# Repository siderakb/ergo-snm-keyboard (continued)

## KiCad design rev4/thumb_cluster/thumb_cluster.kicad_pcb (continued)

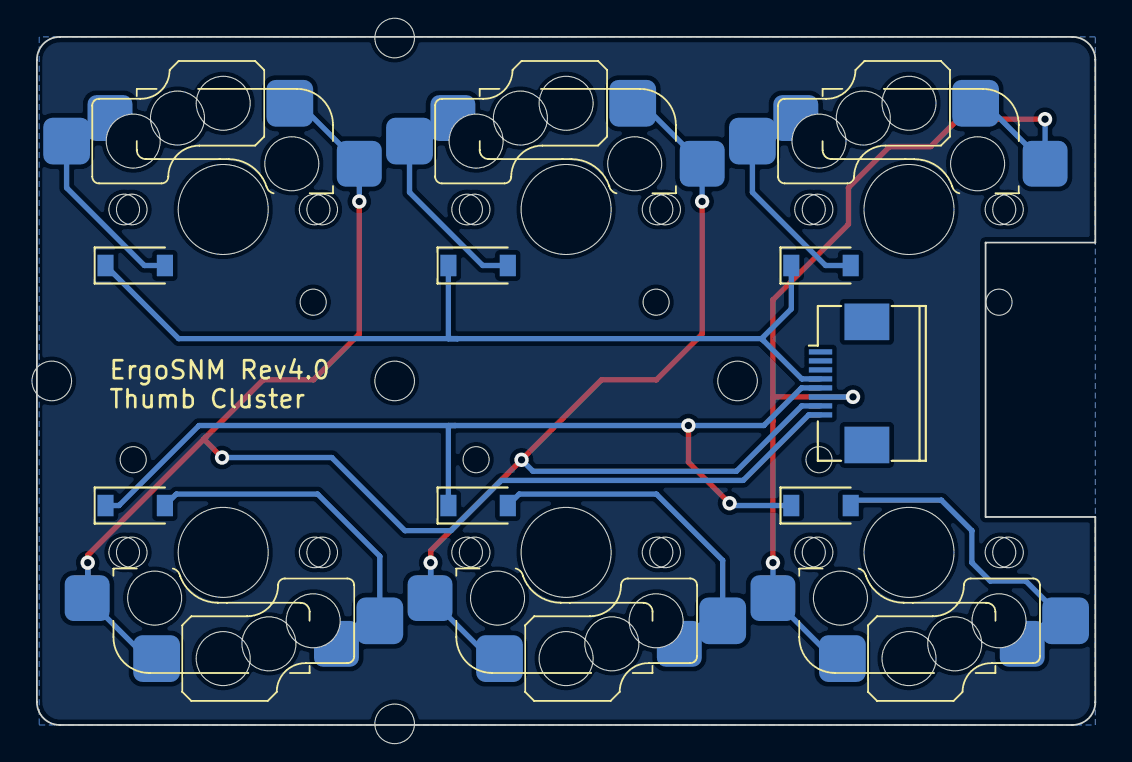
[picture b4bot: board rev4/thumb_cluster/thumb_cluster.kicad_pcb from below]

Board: 2 copper layers, 58.8 x 38.2 mm, 18 parts (11 on the bottom side), 11 nets.

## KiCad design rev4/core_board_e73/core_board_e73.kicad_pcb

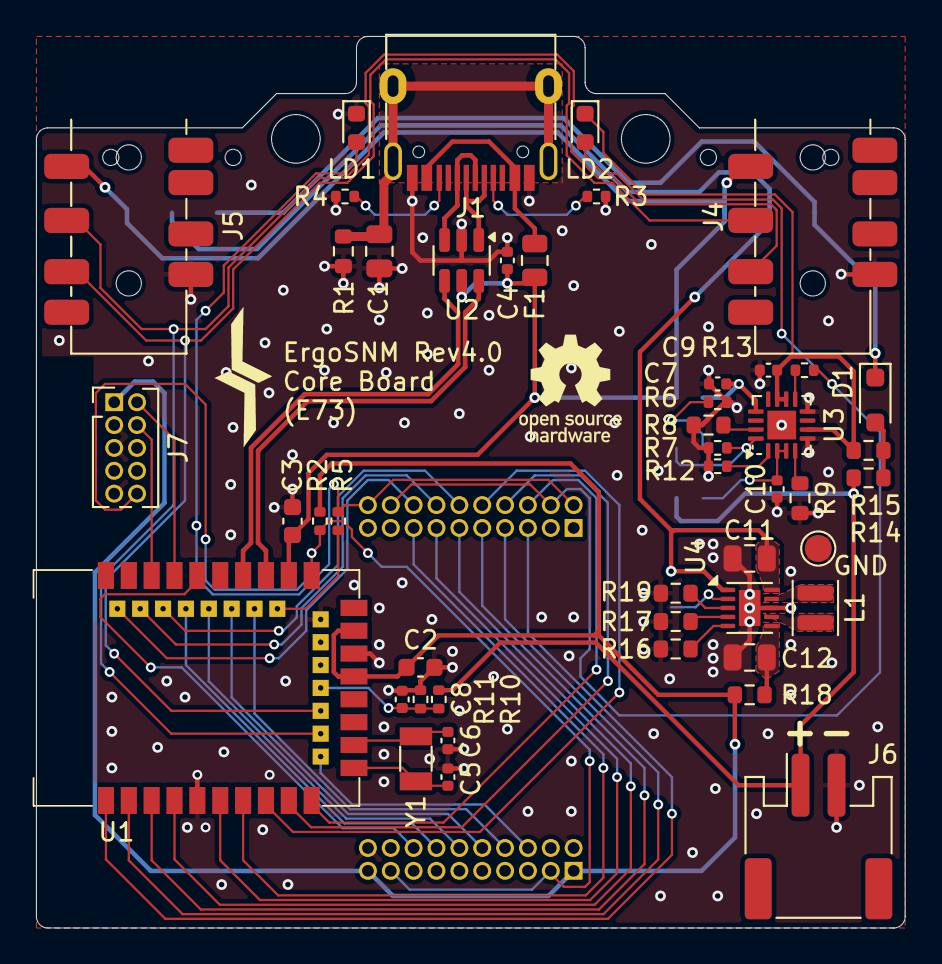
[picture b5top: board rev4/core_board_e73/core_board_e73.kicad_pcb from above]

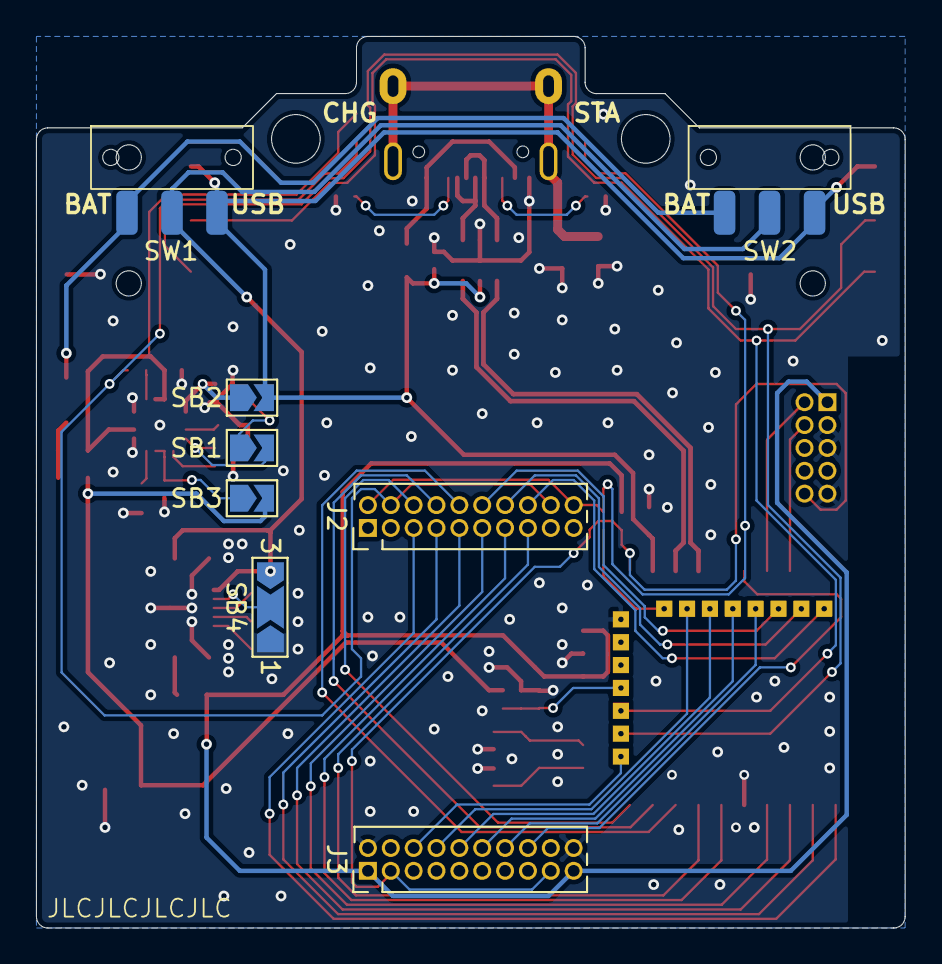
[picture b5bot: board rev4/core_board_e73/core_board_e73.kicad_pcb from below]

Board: 2 copper layers, 48.3 x 49.5 mm, 57 parts (8 on the bottom side), 60 nets.

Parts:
C1: 4.7nF; C_0805_2012Metric
C2, C3: 10uF; C_0603_1608Metric
C4, C8: 100nF; C_0402_1005Metric
C5, C6: 12pF; C_0402_1005Metric
C7: 1uF; C_0402_1005Metric
C9, C10: 4.7uF; C_0402_1005Metric
C11, C12: 22uF; C_0805_2012Metric
D1: B5819; D_SOD-323_HandSoldering
F1: 500mA, 6V; Fuse_0805_2012Metric
H1, H2: MountingHole; MountingHole_2.7mm_M2.5_ISO7380
J1: USB_C_Receptacle_USB2.0; USB_C_Receptacle_HRO_TYPE-C-31-M-12
J2, J3: Conn_02x10_Odd_Even; PinHeader_2x10_P1.27mm_Vertical
J4, J5: PJ-393_TRRS_8P; PJ-393 8P TRRS
J6: Conn_Batt; JST_PH_S2B-PH-SM4-TB_1x02-1MP_P2.00mm_Horizontal
J7: Debug; PinHeader_2x05_P1.27mm_Vertical
L1: 2.2uH; L_Changjiang_FNR252012S
LD1, LD2: LED; LED_0603_1608Metric
R1: 1M; R_0603_1608Metric
R2, R5, R7, R12, R13: 10k; R_0402_1005Metric
R3, R4: 5.1k 1%; R_0402_1005Metric
R6: 2k; R_0402_1005Metric
R8, R9, R14, R15, R18: 0R; R_0603_1608Metric
R10: 820k; R_0402_1005Metric
R11: 2M; R_0402_1005Metric
R16: 15k 1%; R_0603_1608Metric
R17: 0R 1%; R_0603_1608Metric
R19: 20k 1%; R_0603_1608Metric
SB1: Charge Boost; SolderJumper-2_P1.3mm_Open_TrianglePad1.0x1.5mm
SB2: LiPo_CHG; SolderJumper-2_P1.3mm_Open_TrianglePad1.0x1.5mm
SB3: LiPo_BATT; SolderJumper-2_P1.3mm_Open_TrianglePad1.0x1.5mm
SB4: VDD Selection; SolderJumper-3_P2.0mm_Open_TrianglePad1.0x1.5mm_NumberLabels
SW1, SW2: SW_SPDT; 9_3.5_3.5_switch
TP1: GND; TestPoint_Pad_D1.5mm
U1: E73-2G4M08S1C; E73-2G4M08S1C-52840_Hand
U2: USBLC6-2SC6; SOT-23-6
U3: BQ24075RGT; VQFN-16-1EP_3x3mm_P0.5mm_EP1.6x1.6mm
U4: TPS63900; WSON-10-1EP_2.5x2.5mm_P0.5mm_EP1.2x2mm
Y1: 32.768kHz; Crystal_SMD_3215-2Pin_3.2x1.5mm

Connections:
+5V: F1.1, J1.A4 (VBUS), J1.A9 (VBUS), J1.B4 (VBUS), J1.B9 (VBUS)
+BATT: J6.1, R10.1, R14.1, SB3.2 (B)
/power/CONN_D+: J1.A6 (D+), J1.B6 (D+), U2.3 (I/O2)
/power/CONN_D-: J1.A7 (D-), J1.B7 (D-), U2.1 (I/O1)
/power/OUT_SEL: SB4.2 (C), U4.2 (SEL)
/power/USB_SH: C1.1, J1.S1 (SHIELD), R1.1
/power/VBATT_SRC: D1.1 (K), SW1.1 (A), SW2.1 (A)
/power/VIN_DCDC: C11.1, SB4.3 (B), SW1.2 (B), SW2.2 (B), U4.1 (EN), U4.10 (VIN)
/power/VOUT_DCDC: C12.1, R18.2, U4.6 (VOUT)
BAT: C8.1, R10.2, R11.1, U1.18 (P0.04)
CHG_LED: J2.4, J2.18, LD2.2 (A), R13.1
COL_IO_0: J2.6, U1.10 (P0.30)
COL_IO_1: J2.8, U1.9 (P0.31)
COL_IO_2: J2.10, U1.8 (P0.29)
COL_IO_3: J2.12, U1.38 (P1.02)
COL_IO_4: J2.14, U1.40 (P1.04)
COL_IO_5: J2.16, U1.42 (P1.06)
GND: C1.2, C2.2, C3.1, C4.2, C5.1, C6.1, C7.2, C8.2, C9.1, C10.1, C11.2, C12.2, J1.A1 (GND), J1.A12 (GND), J1.B1 (GND), J1.B12 (GND), J3.2, J3.20, J4.T, J5.T, J6.2, J7.3, J7.5, J7.9, LD1.1 (K), R1.2, R3.2, R4.2, R6.2, R7.2, R8.2, R9.2, R11.2, R12.1, R16.2, R17.2, R19.2, SB4.1 (A), TP1.1, U1.5 (GND), U1.21 (GND), U1.24 (GND), U2.2 (GND), U3.5 (EN2), U3.8 (VSS), U3.17 (VSS), U4.8 (GND), U4.11 (GND)
HS_IO_0: J3.6, U1.12 (P0.26)
HS_IO_1: J3.8, U1.30 (P0.17)
HS_IO_2: J3.10, U1.32 (P0.20)
HS_IO_3: J3.12, U1.34 (P0.22)
HS_IO_4: J3.14, U1.36 (P1.00)
HS_IO_5: J3.16, U1.35 (P0.24)
unnamed: D1.2 (A), R14.2, R15.2
unnamed: J1.A5 (CC1), R3.1
unnamed: J1.B5 (CC2), R4.1
unnamed: R6.1, SB1.1 (A)
unnamed: R7.1, SB1.2 (B), U3.16 (ISET)
unnamed: C7.1, SB2.1 (A), U3.13 (IN)
unnamed: C10.2, SB3.1 (A), U3.2 (BAT), U3.3 (BAT)
unnamed: R5.2, U1.28 (P0.15)
unnamed: R8.1, U3.15 (SYSOFF)
unnamed: R12.2, U3.1 (TS)
unnamed: R9.1, U3.4 (~CE)
unnamed: R13.2, U3.9 (~CHG)
unnamed: R19.1, U4.3 (CFG1)
unnamed: R17.1, U4.4 (CFG2)
unnamed: R16.1, U4.5 (CFG3)
unnamed: L1.2, U4.9 (LX1)
unnamed: L1.1, U4.7 (LX2)
RESET: J3.3, J3.17, J7.10, R2.2, U1.26 (P0.18/RST)
ROW_IO_0: J2.5, U1.1 (P1.11)
ROW_IO_1: J2.7, U1.2 (P1.10)
ROW_IO_2: J2.9, U1.3 (P0.03)
ROW_IO_3: J2.11, U1.4 (P0.28)
ROW_IO_4: J2.13, U1.6 (P1.13)
ROW_IO_5: J2.15, U1.7 (P0.02)
RX: J4.R2, J5.R1, U1.16 (P0.08)
STATUS_LED: J2.2, J2.20, LD1.2 (A), R5.1
SWC: J7.4, U1.39 (SWCLK)
SWD: J7.2, U1.37 (SWDIO)
TX: J4.R1, J5.R2, U1.14 (P0.06)
USB_D+: U1.31 (D+), U2.4 (I/O2)
USB_D-: U1.29 (D-), U2.6 (I/O1)
VBUS: C3.2, C4.1, F1.2, J4.S, J5.S, SB2.2 (B), SW1.3 (C), SW2.3 (C), U1.27 (VBUS), U2.5 (VBUS)
VDD: C2.1, J3.1, J3.19, J7.1, R2.1, R18.1, U1.19 (VDD), U1.23 (VDDH)
VDDH: C9.2, LD2.1 (K), R15.1, U3.6 (EN1), U3.10 (OUT), U3.11 (OUT)
XL1: C5.2, U1.11 (P0.00/XL1), Y1.2
XL2: C6.2, U1.13 (P0.01/XL2), Y1.1

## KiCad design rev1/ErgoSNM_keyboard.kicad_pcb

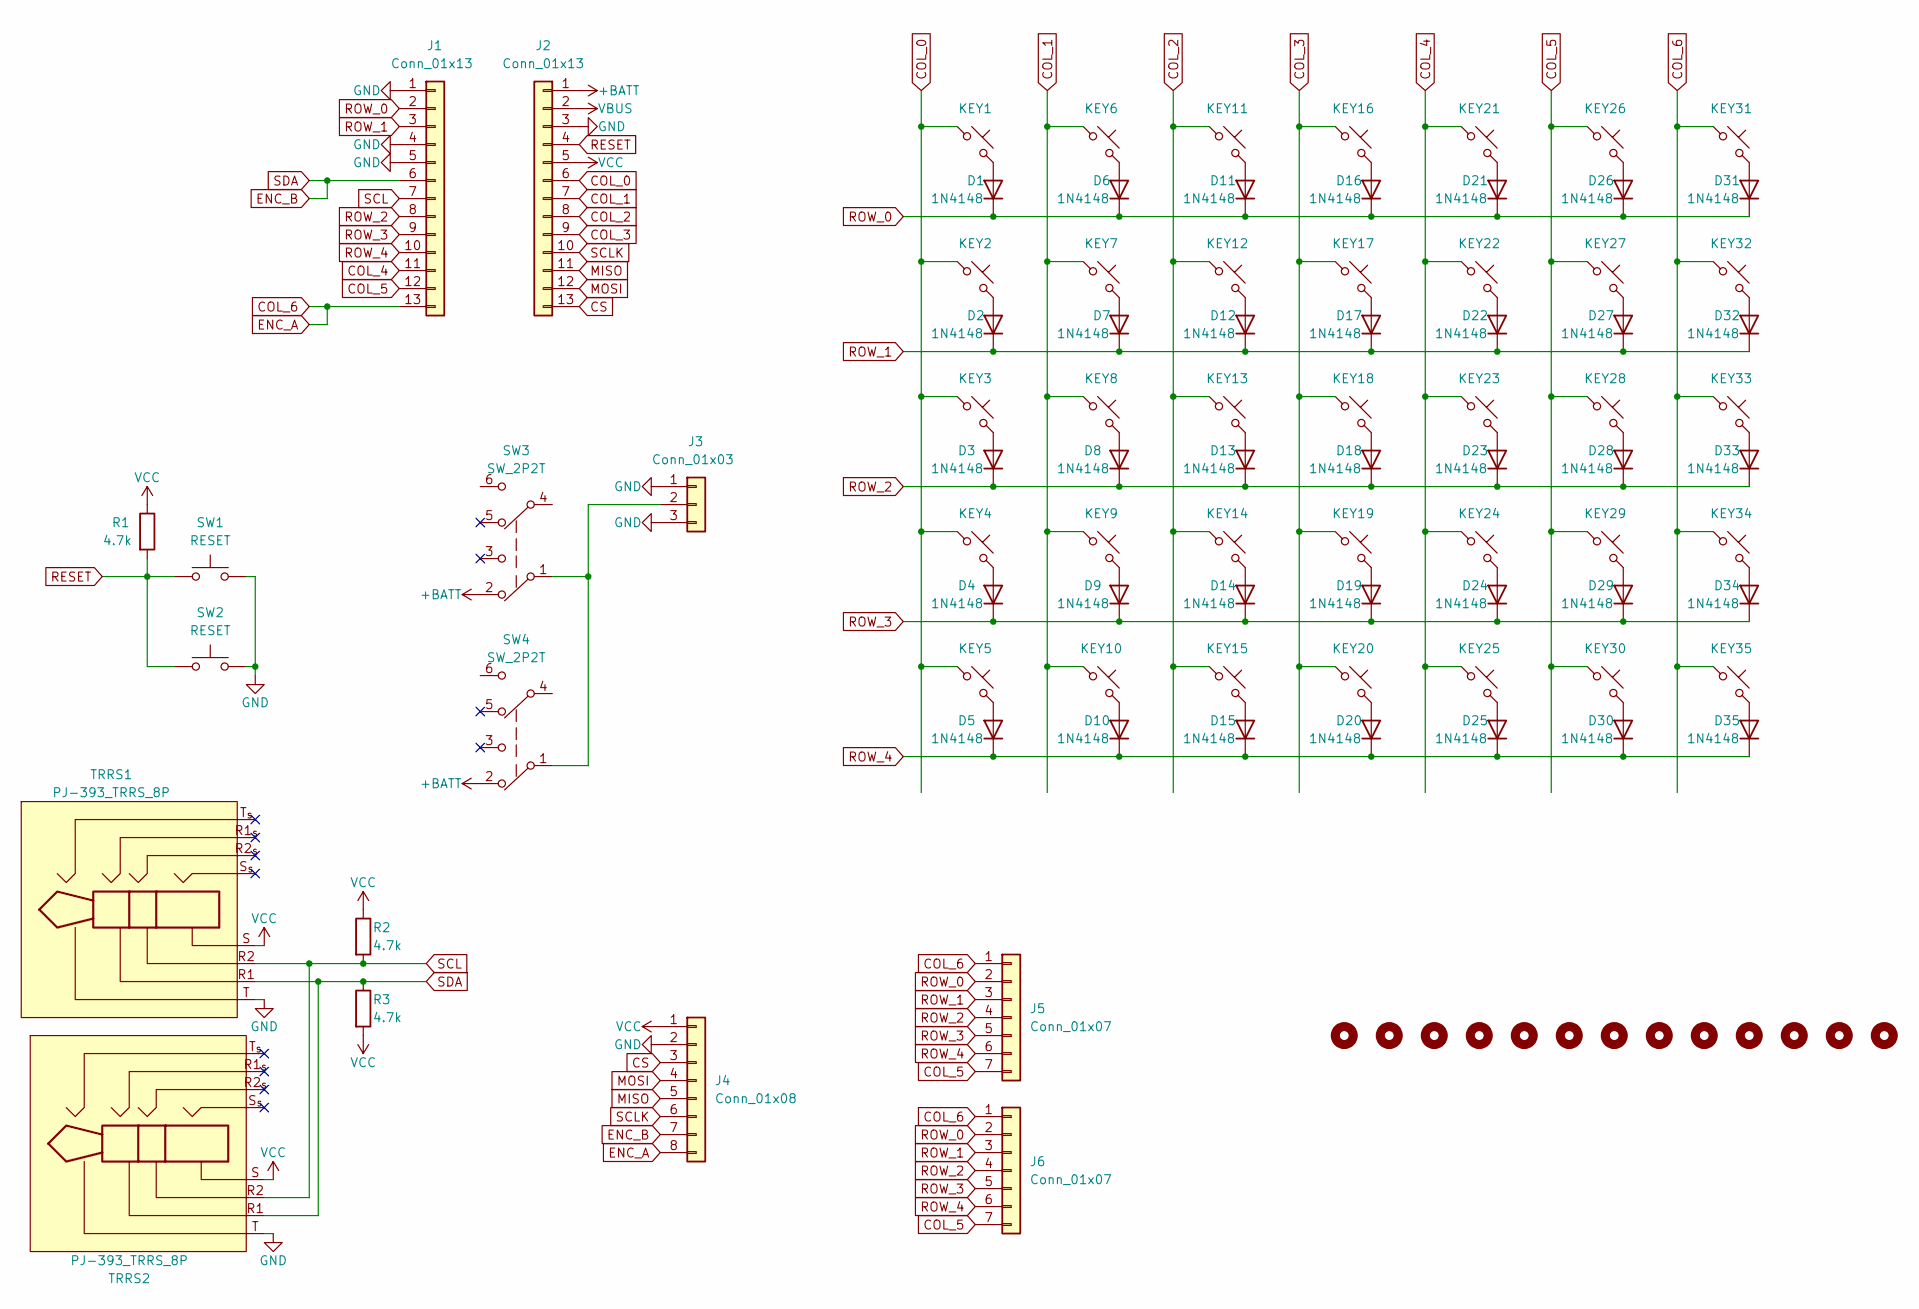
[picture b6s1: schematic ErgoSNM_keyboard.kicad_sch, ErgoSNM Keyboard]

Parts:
D1, D2, D3, D4, D5, D6, D7, D8, D9, D10, D11, D12, D13, D14, D15, D16, D17, D18, D19, D20, D21, D22, D23, D24, D25, D26, D27, D28, D29, D30, D31, D32, D33, D34, D35: 1N4148; D_SOD-123
H1, H2, H3, H4, H5, H6, H7, H8, H9, H10, H11, H12, H13: MountingHole; MountingHole_2.2mm_M2
J1, J2: Conn_01x13; PinSocket_1x13_P2.54mm_Vertical
J3: Conn_01x03; JST_PH_B3B-PH-K_1x03_P2.00mm_Vertical
J4: Conn_01x08; PinSocket_1x08_P2.54mm_Vertical
J5, J6: Conn_01x07; PinHeader_1x07_P2.54mm_Vertical
KEY1, KEY2, KEY3, KEY4, KEY5, KEY6, KEY7, KEY8, KEY9, KEY10, KEY11, KEY12, KEY13, KEY14, KEY15, KEY16, KEY17, KEY18, KEY19, KEY20, KEY21, KEY22, KEY23, KEY24, KEY25, KEY26, KEY27, KEY28, KEY29, KEY30, KEY31, KEY32, KEY33, KEY34, KEY35: SW_Push_45deg; MX_switch_THT_hotswap_double_sided_A
R1, R2, R3: 4.7k; R_0603_1608Metric
SW1, SW2: RESET; SW_SPST_TL3342
SW3, SW4: SW_2P2T; MSK-23D20-T
TRRS1, TRRS2: PJ-393_TRRS_8P; PJ-393 8P TRRS

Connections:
+BATT: J2.1, SW3.2, SW4.2
COL_0: J2.6, KEY1.1, KEY2.1, KEY3.1, KEY4.1, KEY5.1
COL_1: J2.7, KEY6.1, KEY7.1, KEY8.1, KEY9.1, KEY10.1
COL_2: J2.8, KEY11.1, KEY12.1, KEY13.1, KEY14.1, KEY15.1
COL_3: J2.9, KEY16.1, KEY17.1, KEY18.1, KEY19.1, KEY20.1
COL_4: J1.11, KEY21.1, KEY22.1, KEY23.1, KEY24.1, KEY25.1
COL_5: J1.12, J5.7, J6.7, KEY26.1, KEY27.1, KEY28.1, KEY29.1, KEY30.1
COL_6: J1.13, J4.8, J5.1, J6.1, KEY31.1, KEY32.1, KEY33.1, KEY34.1, KEY35.1
CS: J2.13, J4.3
ENC_B: J1.6, J4.7, R3.1, TRRS1.R1, TRRS2.R1
GND: J1.1, J1.4, J1.5, J2.3, J3.1, J3.3, J4.2, SW1.2, SW2.2, TRRS1.T, TRRS2.T
MISO: J2.11, J4.5
MOSI: J2.12, J4.4
unnamed: D1.2 (A), KEY1.2
unnamed: D2.2 (A), KEY2.2
unnamed: D3.2 (A), KEY3.2
unnamed: D4.2 (A), KEY4.2
unnamed: D5.2 (A), KEY5.2
unnamed: D6.2 (A), KEY6.2
unnamed: D7.2 (A), KEY7.2
unnamed: D8.2 (A), KEY8.2
unnamed: D9.2 (A), KEY9.2
unnamed: D10.2 (A), KEY10.2
unnamed: D11.2 (A), KEY11.2
unnamed: D12.2 (A), KEY12.2
unnamed: D13.2 (A), KEY13.2
unnamed: D14.2 (A), KEY14.2
unnamed: D15.2 (A), KEY15.2
unnamed: D16.2 (A), KEY16.2
unnamed: D17.2 (A), KEY17.2
unnamed: D18.2 (A), KEY18.2
unnamed: D19.2 (A), KEY19.2
unnamed: D20.2 (A), KEY20.2
unnamed: D21.2 (A), KEY21.2
unnamed: D22.2 (A), KEY22.2
unnamed: D23.2 (A), KEY23.2
unnamed: D24.2 (A), KEY24.2
unnamed: D25.2 (A), KEY25.2
unnamed: D26.2 (A), KEY26.2
unnamed: D27.2 (A), KEY27.2
unnamed: D28.2 (A), KEY28.2
unnamed: D29.2 (A), KEY29.2
unnamed: D30.2 (A), KEY30.2
unnamed: D31.2 (A), KEY31.2
unnamed: D32.2 (A), KEY32.2
unnamed: D33.2 (A), KEY33.2
unnamed: D34.2 (A), KEY34.2
unnamed: D35.2 (A), KEY35.2
unnamed: J3.2, SW3.1, SW4.1
RESET: J2.4, R1.2, SW1.1, SW2.1
ROW_0: D1.1 (K), D6.1 (K), D11.1 (K), D16.1 (K), D21.1 (K), D26.1 (K), D31.1 (K), J1.2, J5.2, J6.2
ROW_1: D2.1 (K), D7.1 (K), D12.1 (K), D17.1 (K), D22.1 (K), D27.1 (K), D32.1 (K), J1.3, J5.3, J6.3
ROW_2: D3.1 (K), D8.1 (K), D13.1 (K), D18.1 (K), D23.1 (K), D28.1 (K), D33.1 (K), J1.8, J5.4, J6.4
ROW_3: D4.1 (K), D9.1 (K), D14.1 (K), D19.1 (K), D24.1 (K), D29.1 (K), D34.1 (K), J1.9, J5.5, J6.5
ROW_4: D5.1 (K), D10.1 (K), D15.1 (K), D20.1 (K), D25.1 (K), D30.1 (K), D35.1 (K), J1.10, J5.6, J6.6
SCL: J1.7, R2.2, TRRS1.R2, TRRS2.R2
SCLK: J2.10, J4.6
VBUS: J2.2
VCC: J2.5, J4.1, R1.1, R2.1, R3.2, TRRS1.S, TRRS2.S

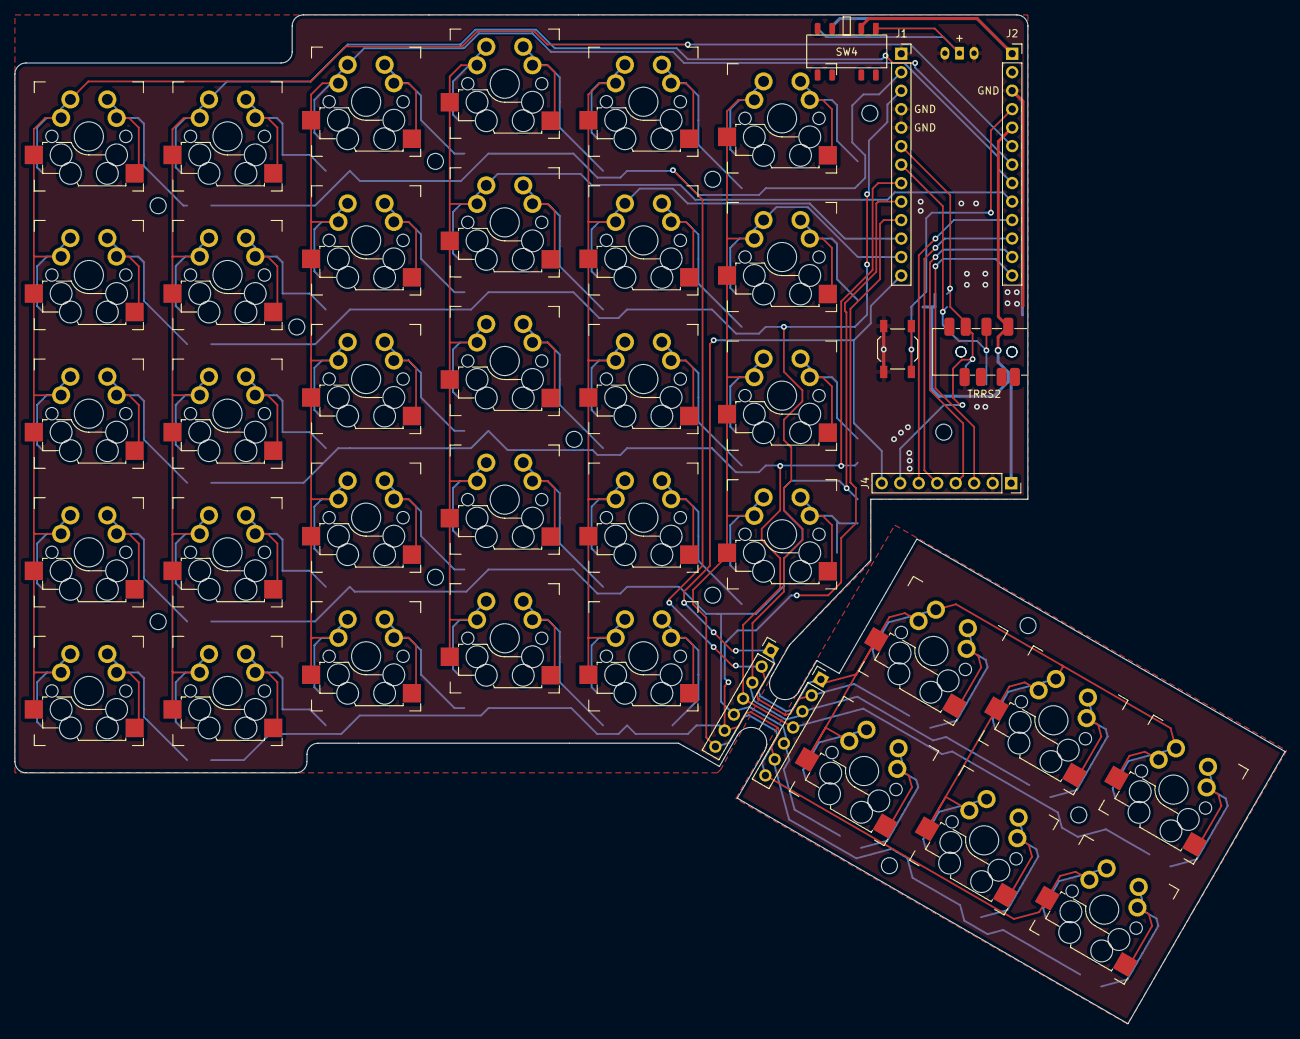
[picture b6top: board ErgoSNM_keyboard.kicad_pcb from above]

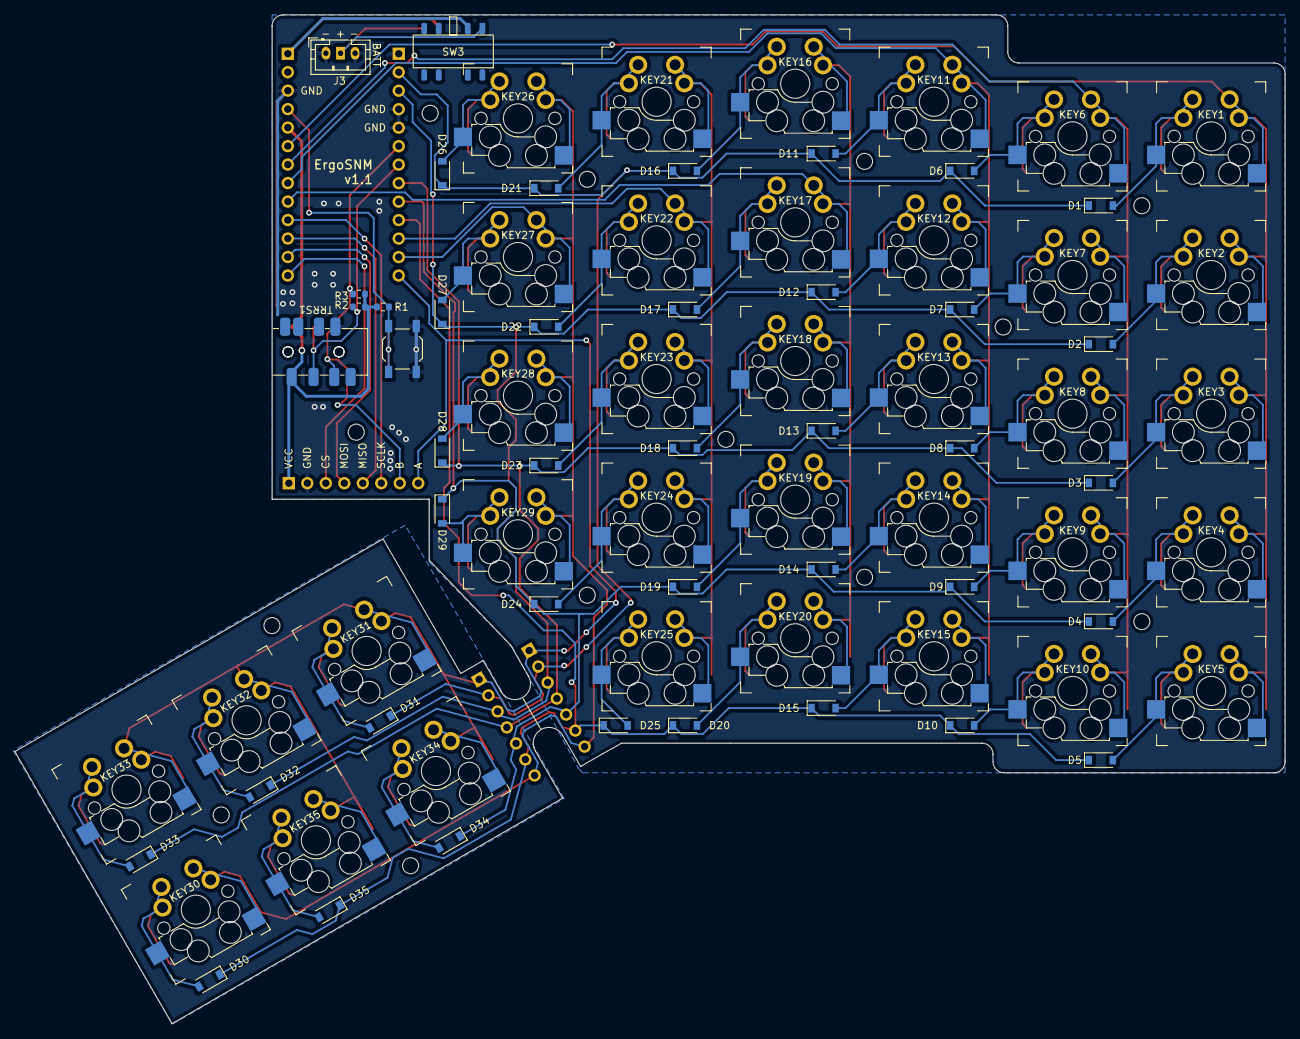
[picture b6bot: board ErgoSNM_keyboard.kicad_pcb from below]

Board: 2 copper layers, 174.5 x 138.6 mm, 98 parts (42 on the bottom side), 58 nets.

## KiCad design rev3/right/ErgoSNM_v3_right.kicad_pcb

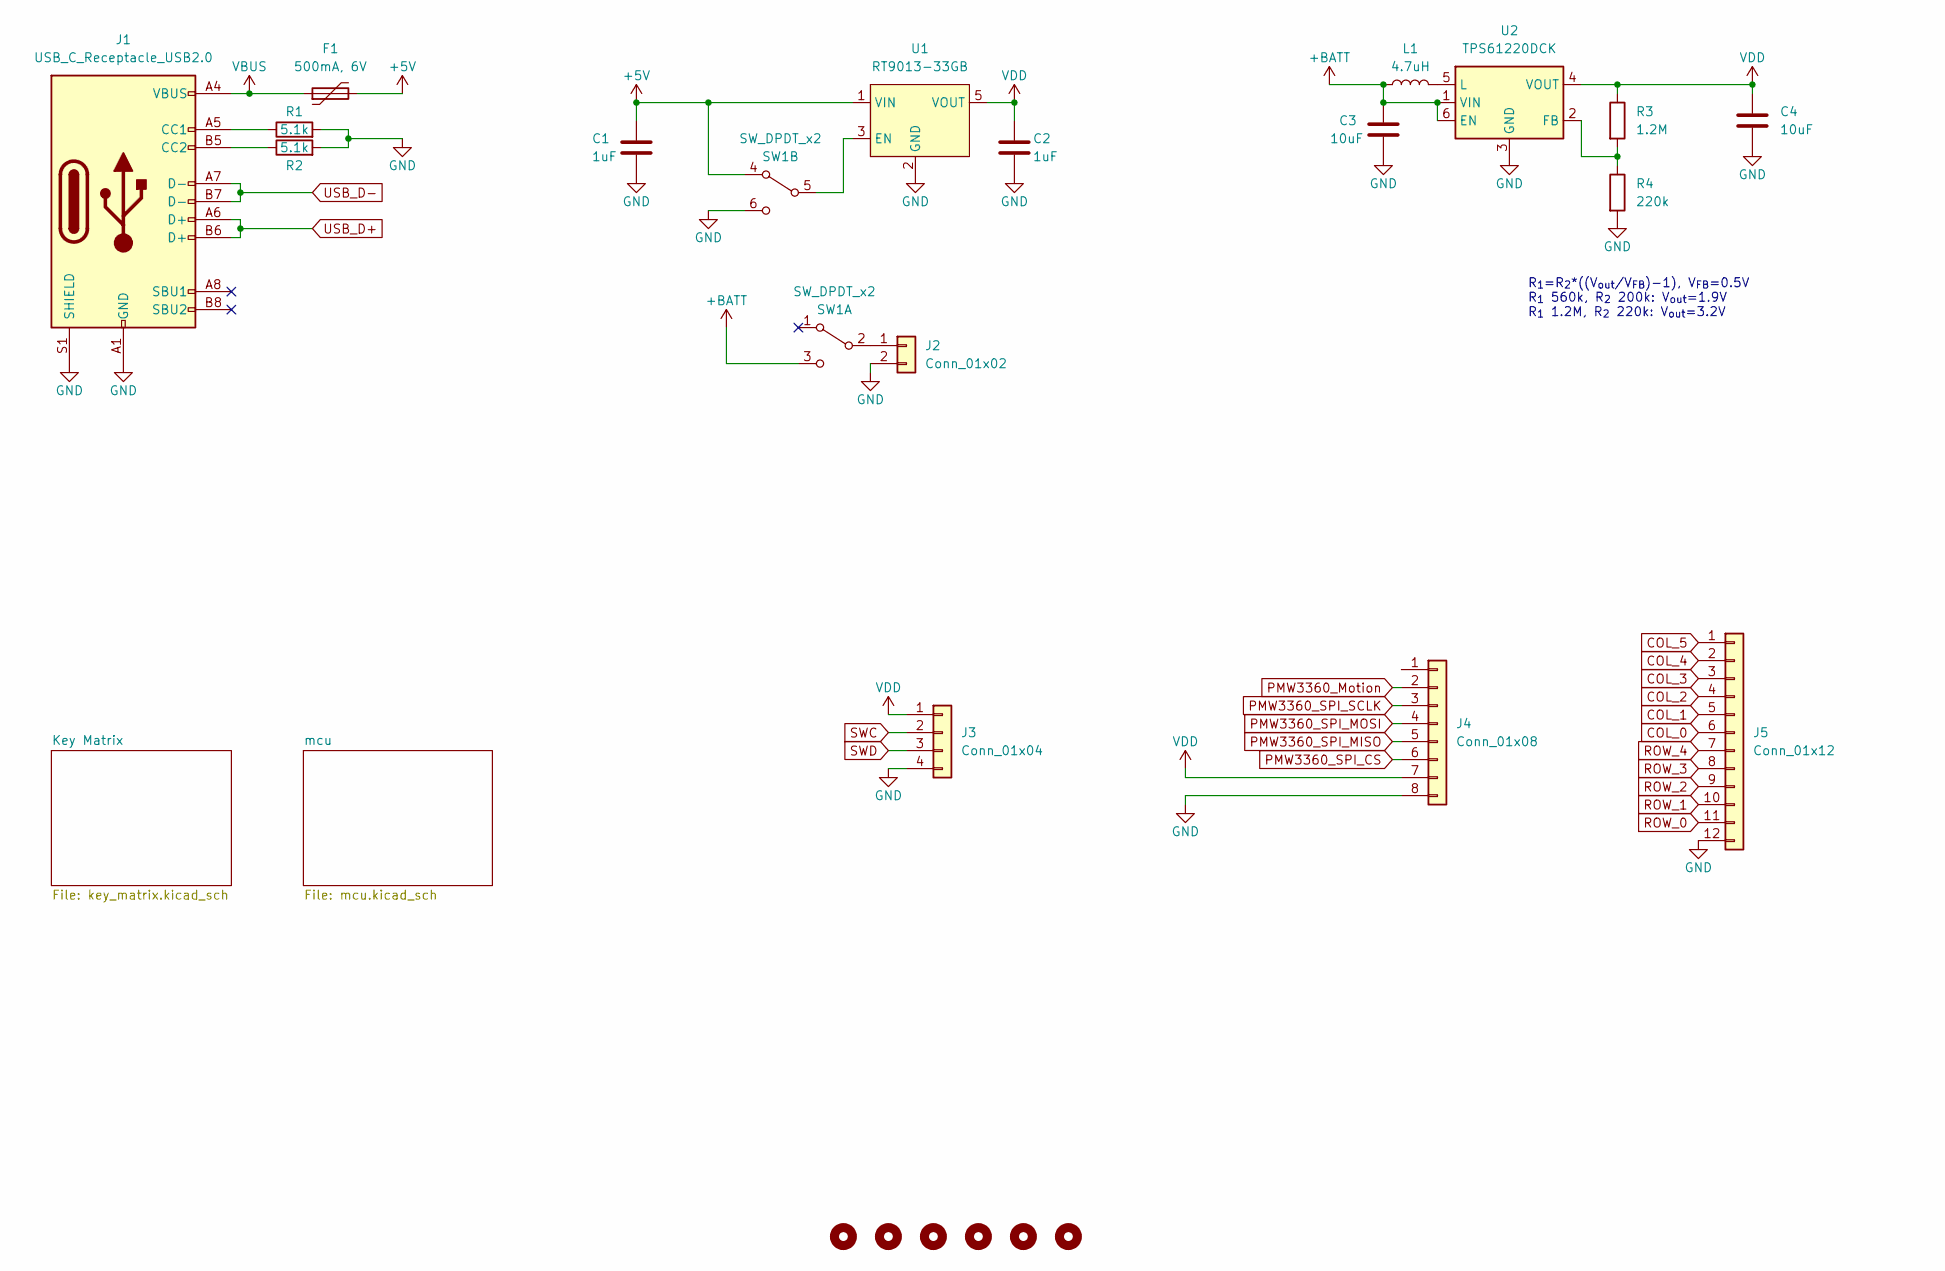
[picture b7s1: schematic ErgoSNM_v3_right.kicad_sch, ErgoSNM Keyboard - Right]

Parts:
C1, C2: 1uF; C_0402_1005Metric; MFR. Part # CL05A105KA5NQNC; LCSC C52923
C3, C4: 10uF; C_0603_1608Metric; MFR. Part # CL05A105KA5NQNC; LCSC C52923
F1: 500mA, 6V; Fuse_0805_2012Metric; MFR. Part # SMD0805B050TF; LCSC C269104
H1, H2, H3, H4, H5, H6: MountingHole; MountingHole_2.2mm_M2
J1: USB_C_Receptacle_USB2.0; USB_C_Receptacle_HRO_TYPE-C-31-M-12; MFR. Part # TYPE-C-31-M-12; LCSC C165948
J2: Conn_01x02; PinHeader_1x02_P2.54mm_Vertical
J3: Conn_01x04; PinHeader_1x04_P2.54mm_Vertical
J4: Conn_01x08; FPC_8P_0.5mm_AFC01-S08FCA-00; MFR. Part # FPC-05F-8PH20; LCSC C2856797
J5: Conn_01x12; PinHeader_1x12_P2.54mm_Vertical
L1: 4.7uH; L_Changjiang_FNR4030S
R1, R2: 5.1k; R_0603_1608Metric; MFR. Part # 0402WGF5101TCE; LCSC C25905
R3: 1.2M; R_0603_1608Metric; MFR. Part # 0402WGF1002TCE; LCSC C25744
R4: 220k; R_0603_1608Metric; MFR. Part # 0402WGF1002TCE; LCSC C25744
SW1: SW_DPDT_x2; MSKT-22D14-T
U1: RT9013-33GB; SOT-23-5; MFR. Part # RT9013-33GB; LCSC C47773
U2: TPS61220DCK; Texas_R-PDSO-G6

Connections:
+5V: C1.1, F1.2, SW1.4 (A), U1.1 (VIN); also elsewhere on the board
+BATT: C3.1, L1.1, SW1.3 (C), U2.1 (VIN), U2.6 (EN)
COL_0: J5.6; also elsewhere on the board
COL_1: J5.5; also elsewhere on the board
COL_2: J5.4; also elsewhere on the board
COL_3: J5.3; also elsewhere on the board
COL_4: J5.2; also elsewhere on the board
COL_5: J5.1; also elsewhere on the board
GND: C1.2, C2.2, C3.2, C4.2, J1.A1 (GND), J1.A12 (GND), J1.B1 (GND), J1.B12 (GND), J1.S1 (SHIELD), J2.2, J3.4, J4.8, J5.12, R1.2, R2.2, R4.2, SW1.6 (C), U1.2 (GND), U2.3 (GND); also elsewhere on the board
unnamed: J1.A5 (CC1), R1.1
unnamed: J1.B5 (CC2), R2.1
unnamed: J2.1, SW1.2 (B)
unnamed: SW1.5 (B), U1.3 (EN)
unnamed: R3.2, R4.1, U2.2 (FB)
unnamed: L1.2, U2.5 (L)
PMW3360_Motion: J4.2; also elsewhere on the board
PMW3360_SPI_CS: J4.6; also elsewhere on the board
PMW3360_SPI_MISO: J4.5; also elsewhere on the board
PMW3360_SPI_MOSI: J4.4; also elsewhere on the board
PMW3360_SPI_SCLK: J4.3; also elsewhere on the board
ROW_0: J5.11; also elsewhere on the board
ROW_1: J5.10; also elsewhere on the board
ROW_2: J5.9; also elsewhere on the board
ROW_3: J5.8; also elsewhere on the board
ROW_4: J5.7; also elsewhere on the board
SWC: J3.2; also elsewhere on the board
SWD: J3.3; also elsewhere on the board
USB_D+: J1.A6 (D+), J1.B6 (D+); also elsewhere on the board
USB_D-: J1.A7 (D-), J1.B7 (D-); also elsewhere on the board
VBUS: F1.1, J1.A4 (VBUS), J1.A9 (VBUS), J1.B4 (VBUS), J1.B9 (VBUS)
VDD: C2.1, C4.1, J3.1, J4.7, R3.1, U1.5 (VOUT), U2.4 (VOUT); also elsewhere on the board

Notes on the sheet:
R_{1}=R_{2}*((V_{out}/V_{FB})-1), V_{FB}=0.5V R_{1} 560k, R_{2} 200k: V_{out}=1.9V R_{1} 1.2M, R_{2} 220k: V_{out}=3.2V

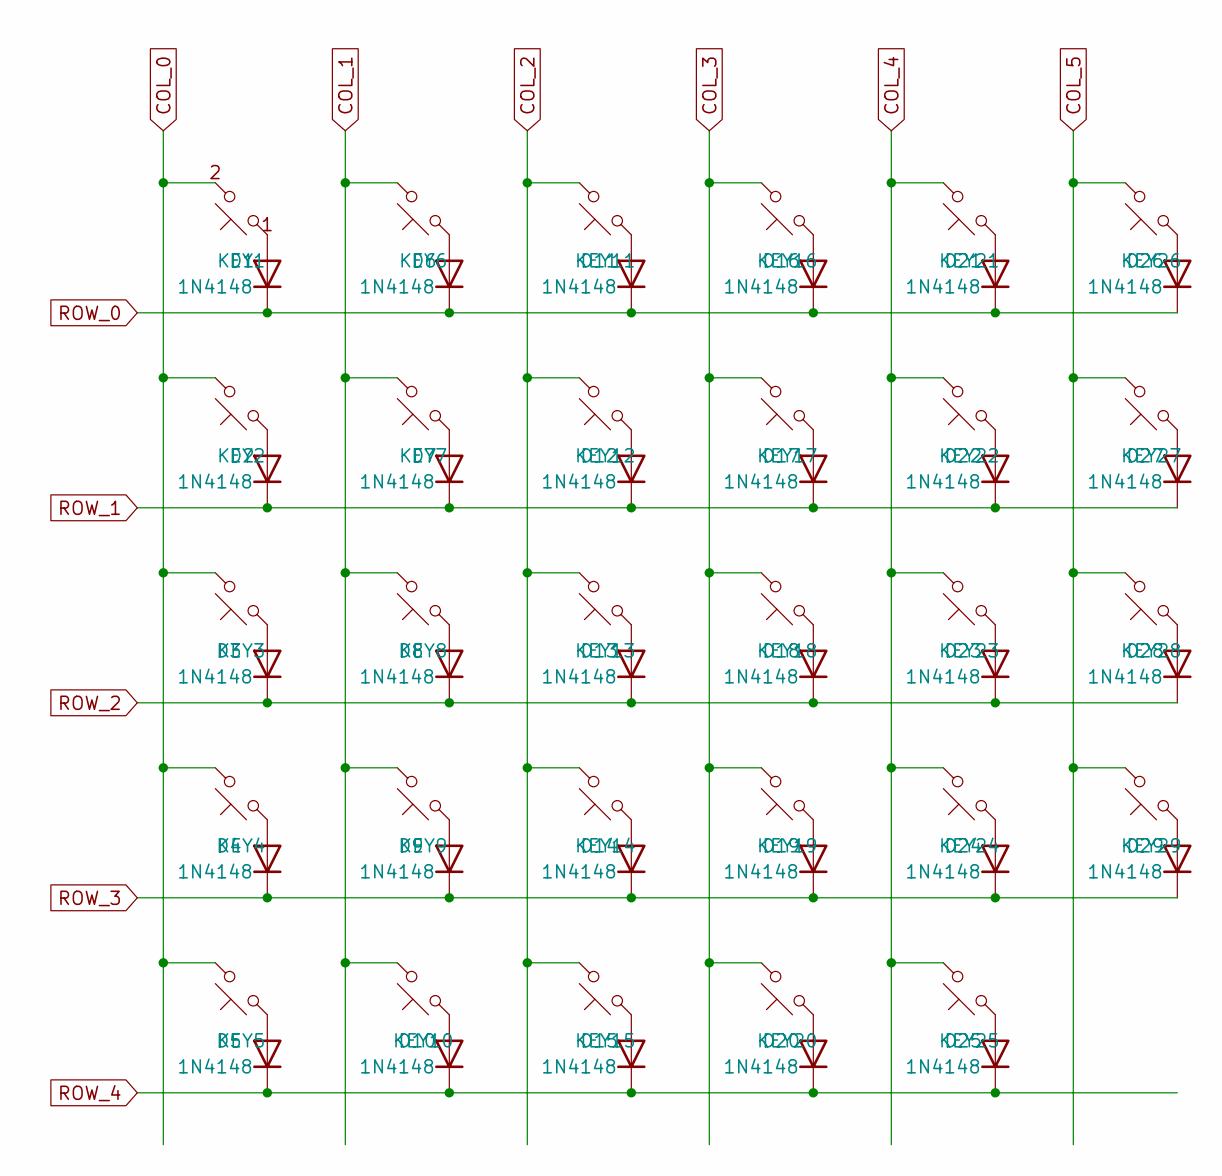
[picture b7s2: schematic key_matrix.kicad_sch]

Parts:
D1, D2, D3, D4, D5, D6, D7, D8, D9, D10, D11, D12, D13, D14, D15, D16, D17, D18, D19, D20, D21, D22, D23, D24, D25, D26, D27, D28, D29: 1N4148; D_SOD-123; MFR. Part # 1N4148W; LCSC C81598
KEY1, KEY2, KEY3, KEY4, KEY5, KEY6, KEY7, KEY8, KEY9, KEY10, KEY11, KEY12, KEY13, KEY14, KEY15, KEY16, KEY17, KEY18, KEY19, KEY20, KEY21, KEY22, KEY23, KEY24, KEY25, KEY26, KEY27, KEY28, KEY29: SW_Push_45deg; SW_MX_HotSwap_PTH

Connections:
COL_0: KEY1.2, KEY2.2, KEY3.2, KEY4.2, KEY5.2; also elsewhere on the board
COL_1: KEY6.2, KEY7.2, KEY8.2, KEY9.2, KEY10.2; also elsewhere on the board
COL_2: KEY11.2, KEY12.2, KEY13.2, KEY14.2, KEY15.2; also elsewhere on the board
COL_3: KEY16.2, KEY17.2, KEY18.2, KEY19.2, KEY20.2; also elsewhere on the board
COL_4: KEY21.2, KEY22.2, KEY23.2, KEY24.2, KEY25.2; also elsewhere on the board
COL_5: KEY26.2, KEY27.2, KEY28.2, KEY29.2; also elsewhere on the board
unnamed: D1.2 (A), KEY1.1
unnamed: D2.2 (A), KEY2.1
unnamed: D3.2 (A), KEY3.1
unnamed: D4.2 (A), KEY4.1
unnamed: D5.2 (A), KEY5.1
unnamed: D6.2 (A), KEY6.1
unnamed: D7.2 (A), KEY7.1
unnamed: D8.2 (A), KEY8.1
unnamed: D9.2 (A), KEY9.1
unnamed: D10.2 (A), KEY10.1
unnamed: D11.2 (A), KEY11.1
unnamed: D12.2 (A), KEY12.1
unnamed: D13.2 (A), KEY13.1
unnamed: D14.2 (A), KEY14.1
unnamed: D15.2 (A), KEY15.1
unnamed: D16.2 (A), KEY16.1
unnamed: D17.2 (A), KEY17.1
unnamed: D18.2 (A), KEY18.1
unnamed: D19.2 (A), KEY19.1
unnamed: D20.2 (A), KEY20.1
unnamed: D21.2 (A), KEY21.1
unnamed: D22.2 (A), KEY22.1
unnamed: D23.2 (A), KEY23.1
unnamed: D24.2 (A), KEY24.1
unnamed: D25.2 (A), KEY25.1
unnamed: D26.2 (A), KEY26.1
unnamed: D27.2 (A), KEY27.1
unnamed: D28.2 (A), KEY28.1
unnamed: D29.2 (A), KEY29.1
ROW_0: D1.1 (K), D6.1 (K), D11.1 (K), D16.1 (K), D21.1 (K), D26.1 (K); also elsewhere on the board
ROW_1: D2.1 (K), D7.1 (K), D12.1 (K), D17.1 (K), D22.1 (K), D27.1 (K); also elsewhere on the board
ROW_2: D3.1 (K), D8.1 (K), D13.1 (K), D18.1 (K), D23.1 (K), D28.1 (K); also elsewhere on the board
ROW_3: D4.1 (K), D9.1 (K), D14.1 (K), D19.1 (K), D24.1 (K), D29.1 (K); also elsewhere on the board
ROW_4: D5.1 (K), D10.1 (K), D15.1 (K), D20.1 (K), D25.1 (K); also elsewhere on the board
